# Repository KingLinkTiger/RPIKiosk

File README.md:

# RPIKiosk
Raspberry Pi Kiosk with Splash Screen

## Day of Setup
1. Setup the FTC Scoring System. Ensure it is powered on, connected to the network, and the software is running.
2. Run Power and Ethernet to the Raspberry Pi
3. Configure the DIP Switches per the configuration guide
4. Power on the Raspberry Pi

## Basic Installation Instructions
1. Raspberry Pi Imager
2. Raspberry Pi OS (Legacy) Lite
3. Configuration to create an account
4. Name: pi
5. Password: mushroom

By default the kiosk assumes the IP of the FTC Scorekeeper software is 192.168.1.101

### Configurations
Changes can be made by modifying /home/pi/.config/openbox/environment
* FTCEVENTSERVER_EVENTCODE - The eventcode for the event. Refer to the FTC scoring system for this value. _NOTE:_ When manually entering an event code you still have to use the DIP Switches to configure the MODE and FIELD.
* FTCEVENTSERVER_IP - IP Address of the FTC server running the scorekeeping software.
* KIOSKURL - URL you would like to display instead of the FTC scoring system (e.g. Twitch Feed)

### Troubleshooting

#### Black Screen
If you receive just a black screen
1. Check the last entries in the log file at /home/pi/RPIKiosk.log.
2. If the log file has not updated recently run the following command to fix the line endings in autostart and reboot.
```sudo dos2unix /etc/xdg/openbox/autostart```

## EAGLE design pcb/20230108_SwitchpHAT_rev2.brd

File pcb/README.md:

# Switch pHAT
## Bill of Materials (BOM)
| Item             | Quantity | Purchase Link                                   |
|------------------|----------|--------------------------------------------------|
| PCB Board        | 1        | [Link](https://www.pcbway.com/)                  |
| 2x20 40-Pin Female Pin Header Socket     | 1       | [Link](https://www.amazon.com/dp/B00R1LLM1M) |
| Dip Switch 8 pin 4 Position  | 2        | [Link](https://www.amazon.com/dp/B07GPSBKSC)     |
| 2x20-pin Strip Dual Male Header (For Pi)       | 1        | [Link](https://www.amazon.com/Break-Away-2x20-pin-Strip-Header-Raspberry/dp/B0756KM7CY)                  |

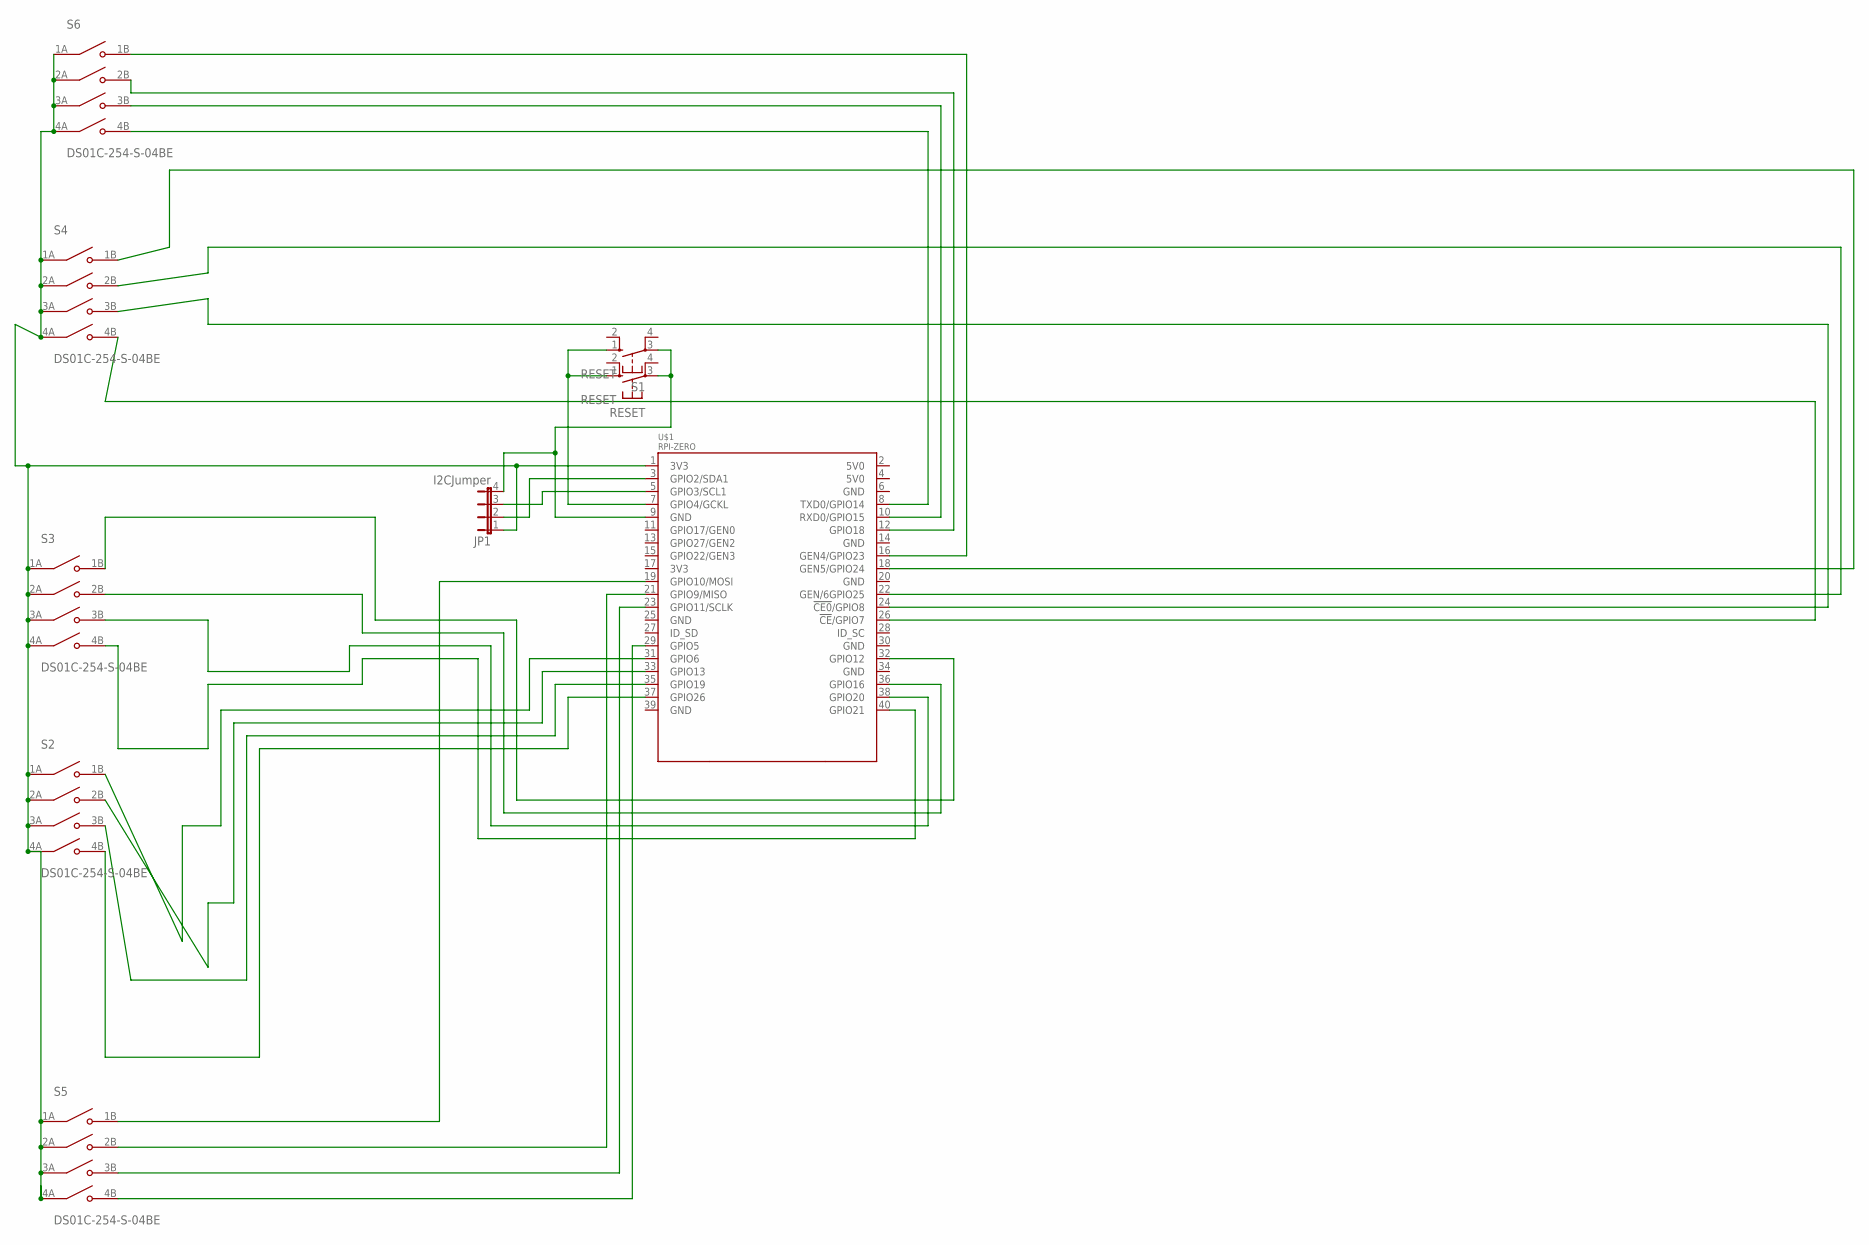
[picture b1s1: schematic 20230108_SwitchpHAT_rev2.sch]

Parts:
JP1: I2CJumper; JP4
RESET: RESET; B3F-40XX
S1: RESET; B3F-10XX
S2, S3, S4, S5, S6: DS01C-254-S-04BE; SW_DS01C-254-S-04BE
U$1: RPI-ZERO; RASPBERRYPI_BASTELSTUBE_V13_RASPI_BOARD_B+_FULL

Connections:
3V3: JP1.1, S2.1A (COM1), S2.2A (COM2), S2.3A (COM3), S2.4A (COM4), S3.1A (COM1), S3.2A (COM2), S3.3A (COM3), S3.4A (COM4), S4.1A (COM1), S4.2A (COM2), S4.3A (COM3), S4.4A (COM4), S5.1A (COM1), S5.2A (COM2), S5.3A (COM3), S5.4A (COM4), S6.1A (COM1), S6.2A (COM2), S6.3A (COM3), S6.4A (COM4), U$1.1 (3V3)
GND: JP1.4, RESET.3, S1.3, U$1.9 (GND)
unnamed: S3.1B (NO1), U$1.32 (GPIO12)
unnamed: S2.4B (NO4), U$1.37 (GPIO26)
unnamed: S2.3B (NO3), U$1.35 (GPIO19)
unnamed: S2.2B (NO2), U$1.33 (GPIO13)
unnamed: S2.1B (NO1), U$1.31 (GPIO6)
unnamed: S4.4B (NO4), U$1.26 (!CE!/GPIO7)
unnamed: S4.3B (NO3), U$1.24 (!CE0!/GPIO8)
unnamed: S3.2B (NO2), U$1.36 (GPIO16)
unnamed: S3.3B (NO3), U$1.38 (GPIO20)
unnamed: S3.4B (NO4), U$1.40 (GPIO21)
unnamed: RESET.1 (S), S1.1 (S), U$1.7 (GPIO4/GCKL)
unnamed: S4.2B (NO2), U$1.22 (GEN/6GPIO25)
unnamed: S4.1B (NO1), U$1.18 (GEN5/GPIO24)
unnamed: S5.4B (NO4), U$1.29 (GPIO5)
unnamed: S5.3B (NO3), U$1.23 (GPIO11/SCLK)
unnamed: S5.2B (NO2), U$1.21 (GPIO9/MISO)
unnamed: S5.1B (NO1), U$1.19 (GPIO10/MOSI)
unnamed: S6.4B (NO4), U$1.8 (TXD0/GPIO14)
unnamed: JP1.2, U$1.3 (GPIO2/SDA1)
unnamed: S6.3B (NO3), U$1.10 (RXD0/GPIO15)
unnamed: S6.2B (NO2), U$1.12 (GPIO18)
unnamed: S6.1B (NO1), U$1.16 (GEN4/GPIO23)
unnamed: JP1.3, U$1.5 (GPIO3/SCL1)

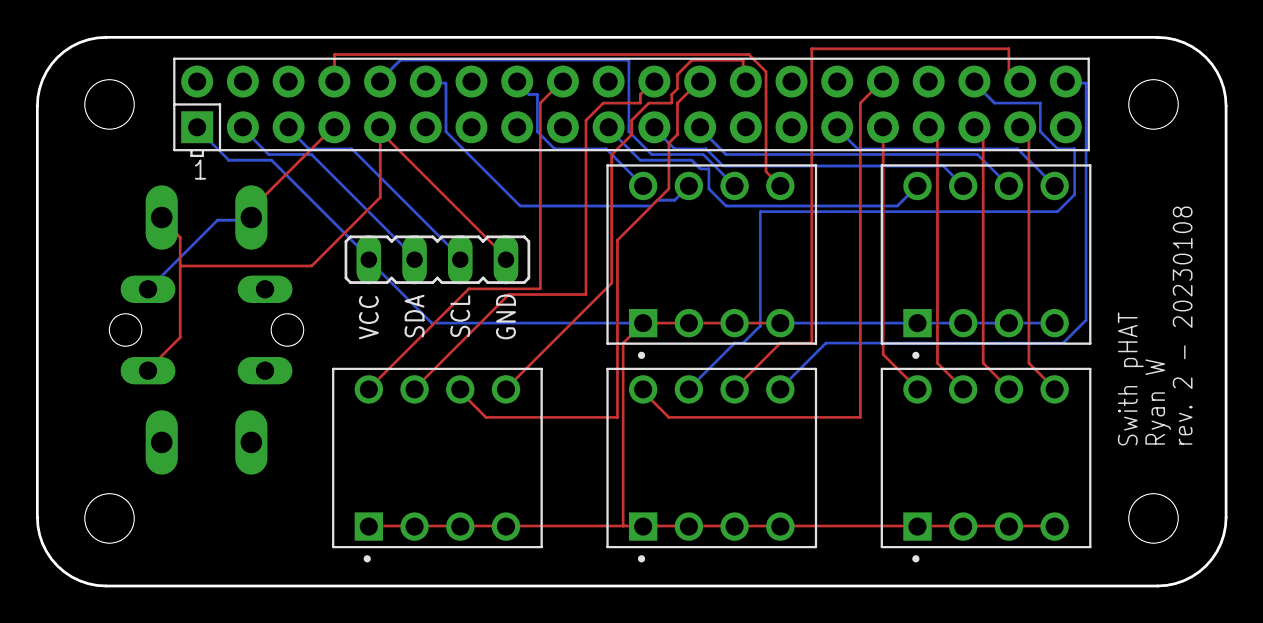
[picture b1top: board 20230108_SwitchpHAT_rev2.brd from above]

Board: 2 copper layers, 66.0 x 30.5 mm, 9 parts (0 on the bottom side), 25 nets.

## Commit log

2019-12-18 Fix Install Line
    Fixed install line. xorg
2019-12-18 Fix Permissions Updating config.txt
    Had to run like 76 as root otherwise you get permission denied when editing /boot/config.txt
2019-12-18 Fix autostart Generation
    Fixed autostart file generation and wrapped the deletion in an if to check if the file exists first.
2019-12-18 .bash_profile Deletion Update
    Wrapped the .bash_profile deletion command in an if statement and am only running it if it exists.
2019-12-18 Moving System Locale and Keyboard Configuration
    Moving system locale and keyboard configuration to the last commands ran as they appear to mess with apt-get.
2019-12-18 Adding Info To Script
    Added information to the top of the script with estimated run time.
2020-01-01 Create openbox Folder if not exist
    Create openbox Folder if not exist
2020-01-16 Timezone
    Added configuration option for timezone update
2020-01-20 Set output volume
    Set output volume to 100%
2021-06-12 Configure Resolution and Update SlashImageURL
    Configure the resolution to 1920x1080 (Group: 2, Mode: 82)
    Updated SPLASHIMAGEURL to MTI Logo
    Updated PI and ROOT passwords to be "MTI"
2021-06-12 Update wget URL
    Updating the wget URL to reflect the MTI branch.
2021-06-12 Debug 1
    Disabling setting the resolution
2021-06-12 Update SPLASHIMAGEURL
    Updated SPLASHIMAGEURL for FIRST's 2021 Season.
2021-06-12 Moving raspi-config to one location
    Moving all raspi-config commands to one section of the script.
2021-06-12 Added su to Pi Account
    Added su command to Pi Account. Moved raspi-config boot behavior and audio to their original locations
2021-06-12 Updating KioskURL
    Updated KioskURL
2022-01-09 Modified config for dashboard
2022-04-06 Update for CHS DCMP 2022
    Update for CHS DCMP 2022
2022-12-10 Update setupKiosk.sh
    Update for FTC 23
2022-12-18 Update setupKiosk.sh
    Automatically find event code via Scorekeeper API. Allow switching field/display via GPIO.
2023-01-08 2023rc1
2023-01-08 Uploading error.html Template
2023-01-08 2023rc2
2023-01-08 2023rc3
2023-01-08 2023rc4
2023-01-08 2023rc5
2023-01-08 2023rc6
2023-01-08 2023rc7
2023-01-08 2023rc8
2023-01-08 2023rc9-final
2023-02-08 Move autostart to own file
    Moved autostart to it's own file.
2023-02-08 Update to separate autostart from script
2023-02-08 Update to include git in the apt installs
2023-02-08 23.1.2
2023-02-08 23.2.3
2023-02-09 23.2.4
2023-02-09 23.2.5
2023-02-09 23.2.6
    Fixed sources.list update
2023-02-10 23.2.7
2023-02-10 23.2.8
2023-12-05 Update setupKiosk.sh
    Change splash image URL for 2024 season
2023-12-05 Update setupKiosk.sh
    Add UMD bookworm distro to sources list.
2023-12-05 Update setupKiosk.sh
    Fix bug creating /home/pi/.config/openbox directory
2023-12-05 Update setupKiosk.sh
    Add check to see if splash.jpg is zero bytes and tries to download again.
2023-12-05 Update autostart
    Debug KIOSKURL
2023-12-05 Update setupKiosk.sh
    Run dos2unix against autostart to ensure file is in unix format.
2023-12-05 Update autostart
    Fixed 2024 bug with handling Dual Divisions
2023-12-05 Update autostart
    Fix bug with autostart autoupdate if local changes were made.
2023-12-05 Update autostart
    Attempt to fix autoupdate function
2023-12-05 Update autostart
    Fix typo in autoupdate if statement
2023-12-05 Update README.md
    Updating readme with some useful information
2023-12-05 Update autostart
    Updated autoupdate code to use more reliable way to check for changes with git.
2023-12-05 Update autostart
    Fix file line endings
2023-12-05 Update setupKiosk.sh
    Fix file line endings
2023-12-05 Update autostart
    Added some else statements for debugging
2023-12-05 Update autostart
    Modify autoupdate to run dos2unix before copying autostart
2023-12-05 Update README.md
    Updating REDAME with additional information
2023-12-10 Update autostart
    Updated to check if FTC Scorekeeper is running on port 8080 as well as port 80
2023-12-10 Update autostart
    Added support for variable FTC Server IP and Port
2023-12-10 Update autostart
    Trying to fix arrIN
2023-12-10 Update autostart
    Commenting out broken code to get event working
2023-12-11 Update autostart
    Removing comment for troubleshooting.
2023-12-11 Update autostart
    Adding additional debugging outputs
2023-12-11 Update autostart
    Fix self_update function
2023-12-11 Update autostart
    Improve IP/Port detection and handling.
2023-12-11 Update autostart
    Fix self_update if statement
2023-12-11 Update autostart
    Improve error message to know if we are ip/port or just ip.
2023-12-11 Update autostart
    Test
2023-12-11 Update autostart
    Improve checking if IP/Port combination is provided.
2023-12-11 Update autostart
    Fixing if statement
2023-12-11 Update autostart
    Fixing if statement again
2023-12-11 Update autostart
    Attempting to fix FIELD dip switches
2023-12-11 Update autostart
    Remove Chromium Preferences file on boot.
2024-04-21 Add License
2024-04-21 Fix spelling and change to generic user
2024-04-21 Create COPYING
    Add GNU General Public License v3.0 to project.
2024-04-21 Update setupKiosk.sh
    Making changes as recommended in PR#2
2024-04-21 Switch pHAT Diagram
2025-01-15 Updated scripts for 24-25 season and bug fixes.
2025-10-20 Create case folder
2025-10-20 Uploading Case 3D Files
    Uploading Case 3D STL and 3mf files.
2025-10-20 Add README with Bill of Materials for Switch pHAT
2025-10-20 Uploading PCB Schematic
